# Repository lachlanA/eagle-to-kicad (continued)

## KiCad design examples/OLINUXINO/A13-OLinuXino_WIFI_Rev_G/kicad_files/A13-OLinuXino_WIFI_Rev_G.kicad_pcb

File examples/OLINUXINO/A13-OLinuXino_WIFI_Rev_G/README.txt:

NOTE: ***** USE AT YOUR OWN RISK *****

This contains the eagle file's from OLIMEX/OLINUXINO from github, which have been Renumbered to work with KiCad
as KiCad will not work correctly with out parts reference ending in a number.
Also note the Eagle files have been converted to version 6.xx of eagle.

*** NOTE: you have to enable LIB prifix in the eagle6xx-sch-to-kicad-sch.ulp even thou is shows you don't need it.
          for some reson Ealge has a lib part which has the same name, as the ground part,  but dose not show up
          when the script searchs for conflicking part names, but show's up on the lib !!!  go figure !!!  ****

source of this project example is at Github address:
   https://github.com/OLIMEX/OLINUXINO/tree/master/HARDWARE/A13-OLinuXino

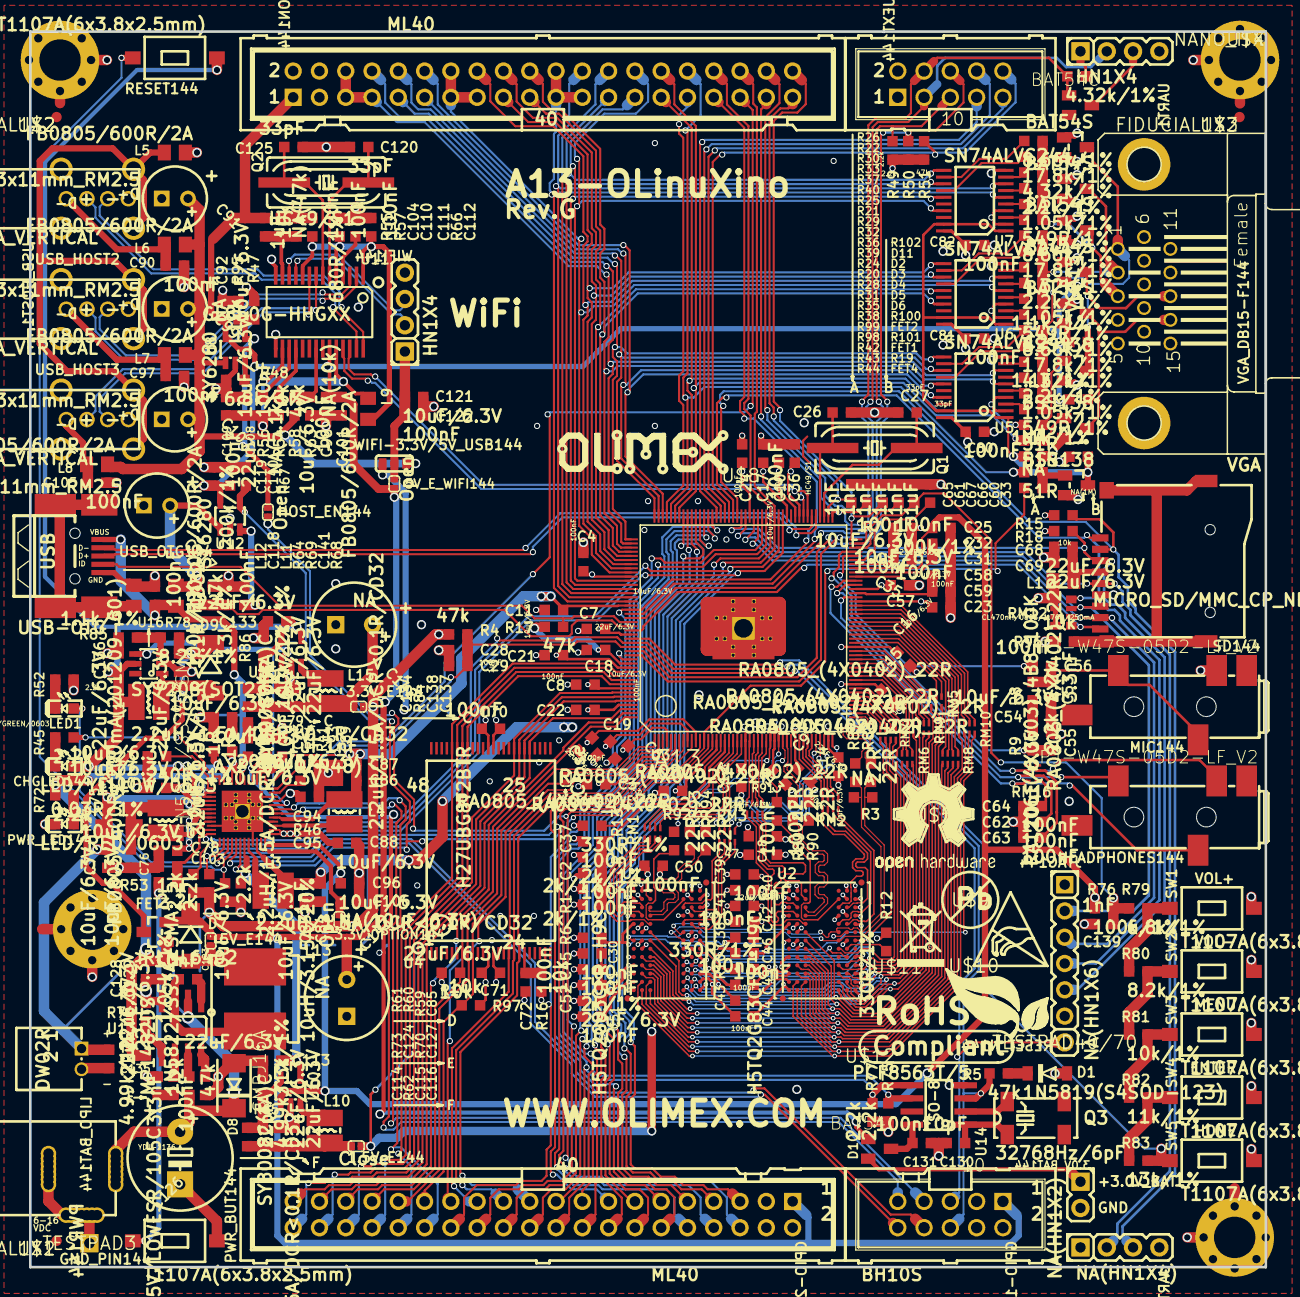
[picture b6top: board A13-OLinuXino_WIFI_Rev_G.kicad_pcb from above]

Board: 4 copper layers, 119.4 x 119.4 mm, 368 parts (0 on the bottom side), 326 nets.

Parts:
1.5V_E144, 3.3V_E144: Close; SJ_1_SMALLER_CLOSE
3.0V_BAT144: NA(HN1X2); HN1X2
3.3V_OPTION144, 5V_E144, 5V_E_WIFI144: Open; SJ_1_SMALLER
C1, C2, C3, C4, C13, C15, C17, C19, C20, C21, C22, C23, C24, C29, C30, C32, C34, C36, C37, C38, C39, C40, C41, C43, C44, C45, C46, C47, C48, C49, C50, C51, C56, C57, C59, C62, C63, C64, C70, C72, C80, C81, C82, C90, C97, C101, C105, C108, C110, C111, C112, C118, C119, C122, C127, C131, C141: 100nF; C0603_DWS
C5, C9, C12, C18, C25, C42, C52, C68, C69, C71, C113, C115, C116, C128, C129, C132, C133, C135, C136, C137, C138: 22uF/6.3V; C0603_DWS
C6, C7, C8, C10, C11, C14, C16, C31, C35, C54, C55, C58, C73, C74, C76, C77, C78, C79, C83, C85, C86, C88, C92, C93, C95, C96, C98, C100, C102, C109, C121: 10uF/6.3V; C0603_DWS
C26, C27, C120, C125: 33pF; C0603_DWS
C28, C33, C75, C89, C94, C104: 1uF; C0603_DWS
C53, C124: 3.3nF; C0603_DWS
C60, C61, C65, C66, C67, C84, C87, C103, C139: 1nF; C0603_DWS
C91, C99, C107, C117: 100uF/16V/LOWESR/105C/6.3x11mm_RM2.5; E2,5-6,3
C106: NA(10uF/6.3V); C0603_DWS
C114: 22pF; C0603_DWS
C123: 10nF; C0603_DWS
C126: 470uF/25V/LOWESR/105C; E5-10,5
C130: 10pF; C0603_DWS
C134: 47pF; C0603_DWS
C140: 22uF; C0603_DWS
C142, C143: NA; E3,5-8
CHGLED144: LED/YELLOW/0603; LED-0603
D1: 1N5819(S4SOD-123); SOD-123
D2, D3, D4, D5, D6: BAT54S; SOT23C(BAT54S)
D7: 1N5822/SS34/SMA; MLL-41
D8: SMBJ16A; DO214AA
D9: 1N5822/SS34/SMA; MELF-MLL41
D10, D11: BAT54C; SOT23C
FET1, FET2, FET4: BSS138; SOT23
FET3: IRLML6402; SOT23
GND_PIN144: TESTPAD3; TEST_PAD40%2f70%2fSQUARE
GPIO-1: BH10S; ML10-MALE
GPIO-2: ML40
HEADPHONES144: PJ-W47S-05D2-LF_V2; PJ-W47S-05D2-LF_5PIN_V2
HOST_EN144: Open; SJ_1_SMALLER
JTAG144: NA(HN1X6); HN1X6
L1: CL470nH/0805/1.76R/250mA; L0805_5MIL_DWS
L2, L3, L4, L10, L14, L15: 2.2uH/1.5A/DCR<0.1R/CD32; CD32
L5, L6, L7, L8, L9, L11: FB0805/600R/2A; L0805_5MIL_DWS
L12: FB0805/600R/200mA(201209-601); L0805_5MIL_DWS
L13: 10uH/3.15A/20%; 8X8MM_3131
LCD_CON144: ML40
LED1: LED/GREEN/0603; LED-0603
LIPO_BAT144: DW02R
MIC144: PJ-W47S-05D2-LF_V2; PJ-W47S-05D2-LF_5PIN_V2
P0, P1, P2, P3, P4, P5, P6, P7, P8, P9, P10, P11, P12: TESTPADTESTPAD_40-ROUND; TESTPAD_40-ROUND
PWR144: YDJ-1136; PWR_JACK_UNI_MILLING
PWR_BUT144: T1107A(6x3.8x2.5mm); SW-TAKT_6X3.5_SMD
PWR_LED144: LED/RED/0603; LED-0603
Q1, Q2: HC49/S1; HC49%2fSMD2_THIN
Q3: 32768Hz/6pF; MC-306
R1, R2, R6, R11: 2k/1%; R0603_5MIL_DWS
R3, R42, R44, R95: NA; R0603_5MIL_DWS
R4, R5, R17, R51, R54, R64, R70: 47k; R0603_5MIL_DWS
R7, R46, R67: 200k/1%; R0603_5MIL_DWS
R8, R9, R45, R49, R50, R52, R53, R59, R60, R61, R72, R73, R75, R77: 2.2k; R0603_5MIL_DWS
R10, R12, R13: 330R/1%; R0603_5MIL_DWS
R14, R16, R18, R47, R55, R56, R96, R97: 10k; R0603_5MIL_DWS
R15: NA(1M); R0603_5MIL_DWS
R19, R85, R100, R101: 1.1k/1%; R0603_5MIL_DWS
R20, R21, R22: 17.8k/1%; R0603_5MIL_DWS
R23: 240R/1%; R0603_5MIL_DWS
R24, R25, R26: 8.66k/1%; R0603_5MIL_DWS
R27: 0.03R/1%; R1206_5MIL_WS
R28, R29, R30, R102: 4.32k/1%; R0603_5MIL_DWS
R31, R32, R33: 2.2k/1%; R0603_5MIL_DWS
R34, R41: 1R; R0603_5MIL_DWS
R35, R36, R37, R74: 1.05k/1%; R0603_5MIL_DWS
R38, R39, R40: 549R/1%; R0603_5MIL_DWS
R43, R98, R99: 51R; R0603_5MIL_DWS
R48, R79: 6.8k/1%; R0603_5MIL_DWS
R57: NA(47k); R0603_5MIL_DWS
R58: NA(5.1k); R0603_5MIL_DWS
R62, R71: 4.99k/1%; R0603_5MIL_DWS
R63: NA(10k); R0603_5MIL_DWS
R65: 3.3k/1%; R0603_5MIL_DWS
R66: 680R/1%; R0603_5MIL_DWS
R68, R83: 13k/1%; R0603_5MIL_DWS
R69, R76, R84: 100k/1%; R0603_5MIL_DWS
R78, R80: 8.2k/1%; R0603_5MIL_DWS
R81: 10k/1%; R0603_5MIL_DWS
R82: 11k/1%; R0603_5MIL_DWS
R86: 22k/1%; R0603_5MIL_DWS
R87, R88, R89, R90, R91, R92, R93, R94: 22R; R0603_5MIL_DWS
RESET144: T1107A(6x3.8x2.5mm); SW-TAKT_6X3.5_SMD
RESET_N144: TESTPAD40/70; TESTPAD
RM1, RM2, RM3, RM4, RM5, RM6, RM7, RM8, RM9, RM10, RM16: RA0805_(4X0402)_22R; R_MATRIX_4_0402_25X625
RM12: RA1206_(4X0603)_4B8_100K; R_MATRIX_4
SD144: MICRO_SD/MMC_CP_NEWTFC-WPAPR-08; TFC-WPAPR-08
SW1, SW2, SW3, SW4, SW5: T1107A(6x3.8x2.5mm); SW-TAKT_6X3.5_SMD
U1, U2: H5TQ2G83CFR-H9C; FBGA78
U3: A13; TQFP176
U4: H27UBG8T2BTR; TSOP48
U5, U6, U7: SN74ALVC244; PW
U8, U12: SY6280; SOT23-5
U9: AXP209(QFN48); QFN48
U10, U15: SY8008C(AA)C; SOT23-5
U11: GL850G-HHGXX; SSOP28
U13: MP1482DS; SOIC8
U14: PCF8563T/5; SO-8
U16: SY7208(SOT23-6); SOT23-6
U$1, U$2, U$3: FIDUCIAL1X2; FIDUCIAL-1X2
U$4: NANO_ITX; NANO-ITX_120X120
U$5: LOGO-OPENHARDWARE_8X8
U$6, U$8: OLIMEX1_V
U$9: PB
U$10: ESD_SYMBOL
U$11: RECYCLE_BIN1%2f8
U$12: ROHS
UART0: NA(HN1X4); HN1X4
UART1: HN1X4
UEXT144: BH10S; ML10-MALE
USB_HOST1, USB_HOST2, USB_HOST3: USB_A_VERTICAL; USB_A_VERTICAL_PTH
USB_OTG144: USB-OTG; USB_MINI_9PIN
VGA_DB15-F144: VGA15; DB15-F_22MM
WIFI144: HN1X4
WIFI-3.3V/5V_USB144: SJ_2_SMALL_12_TIED

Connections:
/#OVCUR1: R58.1, R63.2, U11.21
/+5V: 5V_E144.2, 5V_E_WIFI144.1, C92.1, C98.1, C101.1, C119.1, C140.1, C143.+, D5.2, D6.2, D7.K, FET3.2, GPIO-1.1, GPIO-2.1, LCD_CON144.1, P6.1, R55.2, R100.2, R101.2, U8.5, U11.23, U12.5
/+5V_OTG_PWR: C118.1, L11.1, P12.1, R41.2, U9.31, USB_OTG144.VBUS
/+15V: 5V_E144.1, C128.1, C129.1, D7.A, FET3.1, L13.2, P9.1, R34.2, R71.2, R72.1, U9.32, U9.33
/+24V: C75.2, C77.1, C135.2, LIPO_BAT144.1, P10.1, R27.2, U9.38, U9.39, U9.42
/A0: RM5.1.2, U1.K3, U2.K3
/A1: RM6.3.2, U1.L7, U2.L7
/A2: RM8.3.2, U1.L3, U2.L3
/A3: RM8.4.2, U1.K2, U2.K2
/A4: RM6.4.2, U1.L8, U2.L8
/A5: RM8.2.2, U1.L2, U2.L2
/A6: RM6.2.2, U1.M8, U2.M8
/A7: RM10.2.2, U1.M2, U2.M2
/A8: RM6.1.2, U1.N8, U2.N8
/A9: RM10.4.2, U1.M3, U2.M3
/A10: RM7.3.2, U1.H7, U2.H7
/A11: RM9.4.2, U1.M7, U2.M7
/A12: RM7.1.2, U1.K7, U2.K7
/A13: RM8.1.2, U1.N3, U2.N3
/A14: RM9.3.2, U1.N7, U2.N7
/AVDD: C110.1, C111.1, C112.1, L9.2, U11.1, U11.5, U11.10
/BA0: RM5.2.2, U1.J2, U2.J2
/BA1: RM7.2.2, U1.K8, U2.K8
/BA2: RM5.3.2, U1.J3, U2.J3
/CASN: RM9.1.2, U1.G3, U2.G3
/CKE: RM7.4.2, U1.G9, U2.G9
/CLK: R3.2, R87.1, U1.F7, U2.F7
/CLKN: R3.1, R88.1, U1.G7, U2.G7
/D0: RM1.1.2, U1.B3
/D1: RM3.4.2, U1.C7
/D2: RM1.2.2, U1.C2
/D3: RM3.3.2, U1.C8
/D4: RM1.4.2, U1.E3
/D5: RM3.1.2, U1.E8
/D6: RM1.3.2, U1.D2
/D7: RM3.2.2, U1.E7
/D8: RM2.3.2, U2.C8
/D9: RM4.3.2, U2.D2
/D10: RM2.1.2, U2.E8
/D11: RM4.4.2, U2.E3
/D12: RM2.4.2, U2.C7
/D13: RM4.2.2, U2.C2
/D14: RM2.2.2, U2.E7
/D15: RM4.1.2, U2.B3
/DDR3_A0: RM5.1.1, U3.64
/DDR3_A1: RM6.3.1, U3.52
/DDR3_A2: RM8.3.1, U3.66
/DDR3_A3: RM8.4.1, U3.65
/DDR3_A4: RM6.4.1, U3.51
/DDR3_A5: RM8.2.1, U3.67
/DDR3_A6: RM6.2.1, U3.54
/DDR3_A7: RM10.2.1, U3.71
/DDR3_A8: RM6.1.1, U3.55
/DDR3_A9: RM10.4.1, U3.69
/DDR3_A10: RM7.3.1, U3.48
/DDR3_A11: RM9.4.1, U3.56
/DDR3_A12: RM7.1.1, U3.50
/DDR3_A13: RM8.1.1, U3.68
/DDR3_A14: RM9.3.1, U3.57
/DDR3_BA0: RM5.2.1, U3.63
/DDR3_BA1: RM7.2.1, U3.49
/DDR3_BA2: RM5.3.1, U3.61
/DDR3_CAS: RM9.1.1, U3.59
/DDR3_CK: R87.2, U3.45
/DDR3_CKE: RM7.4.1, U3.47
/DDR3_CK_N: R88.2, U3.46
/DDR3_D0: RM1.1.1, U3.22
/DDR3_D1: RM3.4.1, U3.40
/DDR3_D2: RM1.2.1, U3.21
/DDR3_D3: RM3.3.1, U3.41
/DDR3_D4: RM1.4.1, U3.19
/DDR3_D5: RM3.1.1, U3.44
/DDR3_D6: RM1.3.1, U3.20
/DDR3_D7: RM3.2.1, U3.42
/DDR3_D8: RM2.3.1, U3.37
/DDR3_D9: RM4.3.1, U3.25
/DDR3_D10: RM2.1.1, U3.39
/DDR3_D11: RM4.4.1, U3.24
/DDR3_D12: RM2.4.1, U3.36
/DDR3_D13: RM4.2.1, U3.26
/DDR3_D14: RM2.2.1, U3.38
/DDR3_D15: RM4.1.1, U3.27
/DDR3_DM0: R92.2, U3.29
/DDR3_DM1: R91.2, U3.28
/DDR3_DQS0: R93.2, U3.31
/DDR3_DQS0_N: R94.2, U3.32
/DDR3_DQS1: R89.2, U3.33
/DDR3_DQS1_N: R90.2, U3.34
/DDR3_ODT: RM10.1.2, U1.G1, U2.G1
/DDR3_ODTT: RM10.1.1, U3.72
/DDR3_RAS: RM9.2.1, U3.58
/DDR3_RST: RM10.3.2, U1.N2, U2.N2
/DDR3_RSTT: RM10.3.1, U3.70
/DDR3_WE: RM5.4.1, U3.60
/DM1: U11.27, USB_HOST1.2
/DM2: U11.2, USB_HOST2.2
/DM3: U11.8, USB_HOST3.2
/DM4: U11.11, WIFI144.2
/DP1: U11.28, USB_HOST1.3
/DP2: U11.3, USB_HOST2.3
/DP3: U11.9, USB_HOST3.3
/DP4: U11.12, WIFI144.3
/DQM0: R92.1, U1.B7
/DQM1: R91.1, U2.B7
/DQS0: R93.1, U1.C3
/DQS0_N: R94.1, U1.D3
/DQS1: R89.1, U2.C3
/DQS1_N: R90.1, U2.D3
/DVDD: C108.1, C109.1, L9.1, R54.1, R56.1, U11.16, U11.24
/DZQ: R13.2, U3.17
/EXTEN: U9.20, U15.1, U16.4
/GND: 3.0V_BAT144.2, C2.1, C3.1, C4.1, C5.1, C6.1, C7.1, C8.1, C9.1, C10.1, C11.1, C12.1, C13.1, C14.1, C15.1, C16.1, C17.1, C18.1, C19.1, C20.1, C21.1, C22.1, C23.1, C24.1, C25.1, C26.1, C27.1, C28.1, C29.1, C31.1, C32.1, C33.1, C34.1, C35.1, C36.1, C37.1, C38.1, C39.1, C40.1, C41.1, C42.1, C43.1, C44.1, C45.1, C46.1, C47.1, C48.1, C49.1, C50.1, C51.1, C52.1, C53.1, C54.1, C55.1, C57.1, C58.1, C59.1, C60.1, C61.1, C62.1, C63.1, C64.1, C65.1, C66.1, C67.1, C68.1, C69.1, C70.1, C71.1, C72.1, C73.1, C74.1, C76.2, C77.2, C78.2, C79.1, C80.2, C81.2, C82.2, C83.2, C84.2, C85.2, C86.2, C87.2, C88.2, C89.1, C90.2, C91.-, C92.2, C93.2, C94.1, C95.1, C96.2, C97.2, C98.2, C99.-, C100.2, C101.2, C102.2, C103.1, C104.1, C105.2, C106.2, C107.-, C108.2, C109.2, C110.2, C111.2, C112.2, C113.2, C115.2, C116.2, C117.-, C118.2, C119.2, C120.1, C121.2, C122.2, C125.1, C126.-, C127.2, C128.2, C129.2, C130.2, C131.1, C132.2, C133.2, C135.1, C136.1, C137.2, C138.2, C139.2, C140.2, C141.2, C142.-, C143.-, D2.1, D3.1, D4.1, D5.1, D6.1, D8.A, GND_PIN144.P$1, GPIO-1.2, GPIO-1.4, GPIO-2.2, GPIO-2.4, JTAG144.6, L5.1, L12.1, LCD_CON144.2, LCD_CON144.4, LIPO_BAT144.2, MIC144.5, P0.1, PWR144.-, PWR144.--, PWR_BUT144.P$1, PWR_LED144.C, R2.1, R7.2, R10.1, R11.1, R12.1, R13.1, R15.2, R23.1, R42.1, R46.1, R48.1, R52.1, R57.2, R59.1, R63.1, R65.2, R66.1, R67.1, R68.1, R69.1, R73.2, R74.2, R85.2, R86.2, R95.1, R96.2, SD144.6, SW1.P$1, SW2.P$1, SW3.P$1, SW4.P$1, SW5.P$1, U1.A1, U1.A8, U1.B1, U1.B2, U1.B8, U1.C9, U1.D1, U1.D8, U1.D9, U1.F2, U1.F8, U1.H2, U1.J1, U1.J9, U1.L1, U1.L9, U1.N1, U1.N9, U2.A1, U2.A8, U2.B1, U2.B2, U2.B8, U2.C9, U2.D1, U2.D8, U2.D9, U2.F2, U2.F8, U2.H2, U2.J1, U2.J9, U2.L1, U2.L9, U2.N1, U2.N9, U3.79, U3.GND_, U4.13, U4.36, U5.2, U5.4, U5.10, U6.2, U6.4, U6.10, U7.2, U7.4, U7.10, U8.2, U9.9, U9.16, U9.22, U9.46, U9.VSS, U10.2, U11.14, U11.15, U12.2, U13.4, U14.4, U15.2, U16.2, U$4.GND, U$4.P$2, U$4.P$3, U$4.P$4, UART0.4, UART1.4, UEXT144.2, USB_HOST1.4, USB_HOST2.4, USB_HOST3.4, USB_OTG144.GND, VGA_DB15-F144.5, VGA_DB15-F144.6, VGA_DB15-F144.7, VGA_DB15-F144.8, VGA_DB15-F144.10, WIFI144.4
/IPSOUT: C73.2, C78.1, C85.1, C88.1, C95.2, C102.1, C113.1, C133.1, C136.2, CHGLED144.A, L14.1, P5.1, RESET144.P$2, U9.7, U9.13, U9.14, U9.21, U9.34, U9.35, U9.40, U9.44, U10.4, U15.4, U16.5
/LCD_CLK: LCD_CON144.31, U3.129
/LCD_D2: LCD_CON144.21, LCD_CON144.22, LCD_CON144.23, U3.148, U7.6
/LCD_D3: LCD_CON144.24, U3.147, U7.8
/LCD_D4: LCD_CON144.25, U3.146, U7.11
/LCD_D5: LCD_CON144.26, U3.145, U7.13
/LCD_D6: LCD_CON144.27, U3.144, U7.15
/LCD_D7: LCD_CON144.28, U3.143, U7.17
/LCD_D10: LCD_CON144.13, LCD_CON144.14, LCD_CON144.15, U3.141, U6.6
/LCD_D11: LCD_CON144.16, U3.140, U6.8
/LCD_D12: LCD_CON144.17, U3.139, U6.11
/LCD_D13: LCD_CON144.18, U3.138, U6.13
/LCD_D14: LCD_CON144.19, U3.137, U6.15
/LCD_D15: LCD_CON144.20, U3.136, U6.17
/LCD_D18: LCD_CON144.5, LCD_CON144.6, LCD_CON144.7, U3.135, U5.6
/LCD_D19: LCD_CON144.8, U3.134, U5.8
/LCD_D20: LCD_CON144.9, U3.133, U5.11
/LCD_D21: LCD_CON144.10, U3.132, U5.13
/LCD_D22: LCD_CON144.11, U3.131, U5.15
/LCD_D23: LCD_CON144.12, U3.130, U5.17
/LCD_DE: LCD_CON144.32, R43.1, U3.128
/LCD_HSYNC: LCD_CON144.29, R99.1, U3.127
/LCD_VSYNC: LCD_CON144.30, R98.1, U3.126
/LRADC: C60.2, C139.1, R76.2, R79.1, U3.86
/N$1: C58.2, C59.2, U3.75
/N$2: C30.2, C38.2, C45.2, C46.2, R6.1, R11.2, U1.E1, U1.J8, U2.E1, U2.J8
/N$3: R10.2, U1.H8
/N$4: R45.2, U9.36
/N$5: R12.2, U2.H8
/N$6: HOST_EN144.2, R47.2, R95.2, U8.4
/N$7: R96.1, SD144.10, SD144.11, SD144.12, SD144.13
/N$8: L10.1, U10.3
/N$9: C31.2, C32.2, U3.80
/N$11: 5V_E_WIFI144.2, C121.1, C122.1, WIFI144.1, WIFI-3.3V/5V_USB144.2
/N$13: C33.2, U3.83
/N$14: C34.2, C35.2, R7.1, U3.82
/N$16: C53.2, C56.1, MIC144.2, MIC144.3, R8.2
/N$18: 1.5V_E144.1, C114.1, C115.1, C116.1, L10.2, R62.1
/N$19: C114.2, R62.2, R65.1, U10.5
/N$20: R37.1, U7.5
/N$21: R43.2, R44.1
/N$22: C54.2, R8.1, R9.2
/N$23: C132.1, D9.1, FET3.3, R78.2
/N$24: C131.2, D10.3, U14.8
/N$25: C56.2, U3.84
/N$26: HEADPHONES144.2, RM16.2.2, U3.74
/N$27: HEADPHONES144.5, RM16.3.2, U3.77
/N$28: HEADPHONES144.3, RM16.1.2, U3.78
/N$29: 3.0V_BAT144.1, D10.2
/N$30: D11.3, UART1.3
/N$31: C126.+, D8.C, P8.1, PWR144.+, R70.1, U13.2
/N$34: C62.2, RM16.2.1
/N$35: C63.2, RM16.3.1
/N$36: C127.1, U13.8
/N$37: R70.2, U13.7
/N$38: PWR_BUT144.P$2, R53.1
/N$42: LED1.C, R52.2
/N$43: CHGLED144.C, R45.1
/N$44: C64.2, RM16.1.1
/N$46: C123.1, U13.1
/N$50: C123.2, L13.1, U13.3
/N$60: C124.1, U13.6
/N$61: C124.2, R73.1
/N$62: R71.1, R74.1, U13.5
/N$64: L15.1, U15.3
/N$65: 3.3V_E144.1, C134.1, C137.1, C138.1, C142.+, L15.2, R84.1
/N$66: C134.2, R84.2, R86.1, U15.5
/N$88: R79.2, R80.1, SW1.P$2
/N$89: R80.2, R81.1, SW2.P$2
/N$90: R81.2, R82.1, SW3.P$2
/N$91: R82.2, R83.1, SW4.P$2
/N$99: R68.2, U12.3
/N$100: C117.+, L11.2, R64.2, U12.1
/N$101: R48.2, U8.3
/N$102: R66.2, U11.4
/N$103: R40.1, U7.3
/N$104: R30.1, U7.9
/N$105: R54.2, U11.18
/N$106: R56.2, U11.17
/N$107: R33.1, U7.7
/N$108: R22.1, U7.14
/N$109: R26.1, U7.12
/N$110: L5.2, USB_HOST1.P$3, USB_HOST1.P$4, USB_HOST2.P$3, USB_HOST2.P$4, USB_HOST3.P$3, USB_HOST3.P$4
/N$111: C90.1, L6.2, USB_HOST1.1
/N$112: C97.1, L7.2, USB_HOST2.1
/N$113: C105.1, L8.2, USB_HOST3.1
/N$114: C91.+, C99.+, C107.+, L6.1, L7.1, L8.1, R58.2, U8.1, WIFI-3.3V/5V_USB144.1
/N$117: R29.1, U6.9
/N$118: R32.1, U6.7
/N$119: C104.2, R55.1, R57.1, U11.13
/N$120: R46.2, U9.23
/N$121: C130.1, Q3.1, U14.1
/N$122: Q3.4, U14.2
/N$123: D9.2, L14.2, U16.1
/N$124: C72.2, R16.2, U4.19
/N$125: R23.2, U9.37
/N$126: R78.1, R85.1, U16.3
/N$127: L2.1, U9.45
/N$128: C75.1, C76.1, L2.2, R27.1, U9.43
/N$129: PWR_LED144.A, R72.2
/N$130: L3.1, U9.8
/N$131: L4.1, U9.15
/N$132: C94.2, U9.24
/N$133: 3.3V_OPTION144.1, C106.1, U9.11
/N$134: C74.2, R34.1
/N$135: C79.2, R41.1
/N$138: R36.1, U6.5
/N$139: C103.2, R53.2, U9.47
/N$140: R59.2, RESET144.P$1, U9.4
/N$172: R39.1, U6.3
/N$173: R21.1, U6.14
/N$174: R25.1, U6.12
/N$177: R28.1, U5.9
/N$178: R31.1, U5.7
/N$179: R35.1, U5.5
/N$180: R38.1, U5.3
/N$181: R20.1, U5.14
/N$182: R24.1, U5.12
/N$266: L12.2, USB_OTG144.GND1, USB_OTG144.GND2, USB_OTG144.GND3, USB_OTG144.GND4
/NMI_N: GPIO-1.6, R5.1, U3.158, U9.48, U14.3
/PIN0: GPIO-1.7, LCD_CON144.35, U9.19
/PIN1: GPIO-1.9, U9.18
/PIN2: GPIO-1.10, U9.5
/PIN3: GPIO-1.8, U9.3
/PIN4/TWI0-SCK: GPIO-2.5, R60.1, U3.101, U9.2
/PIN5/TWI0-SDA: GPIO-2.7, R61.1, U3.102, U9.1
/PIN6/PWM0: GPIO-2.9, LCD_CON144.36, U3.103
/PIN7: GPIO-2.11, LCD_CON144.33, U3.150
/PIN8: GPIO-2.13, LCD_CON144.34, U3.104
/PIN9: GPIO-2.15, U3.10
/PIN10/TWI1-SCK: GPIO-2.17, R75.1, U3.105, U14.6
/PIN11/TWI1-SDA: GPIO-2.19, R77.1, U3.106, U14.5
/PIN12/NWE: GPIO-2.21, U3.8, U4.18
/PIN13/NALE: GPIO-2.23, U3.7, U4.17
/PIN14/NCLE: GPIO-2.25, U3.6, U4.16
/PIN15/NCE1: GPIO-2.27, U3.3
/PIN16/NCE0: GPIO-2.29, R97.2, U4.9
/PIN17/NRE: GPIO-2.31, U3.1, U4.8
/PIN18/NRB0: GPIO-2.33, R14.2, U3.176, U4.7
/PIN19/NRB1: GPIO-2.35, U3.175
/PIN20/NDQ0: GPIO-2.37, U3.174, U4.29
/PIN21/NDQ1: GPIO-2.39, U3.172, U4.30
/PIN22/NDQ2: GPIO-2.40, U3.171, U4.31
/PIN23/NDQ3: GPIO-2.38, U3.170, U4.32
/PIN24/NDQ4: GPIO-2.36, U3.168, U4.41
/PIN25/NDQ5: GPIO-2.34, U3.167, U4.42
/PIN26/NDQ6: GPIO-2.32, U3.166, U4.43
/PIN27/NDQ7: GPIO-2.30, U3.165, U4.44
/PIN28/NDQS: GPIO-2.28, U3.162
/PIN29: GPIO-2.26, U3.118
/PIN30: GPIO-2.24, U3.119
/PIN31: GPIO-2.22, U3.120
/PIN32: GPIO-2.20, U3.121
/PIN33: GPIO-2.18, U3.122
/PIN34: GPIO-2.16, U3.123
/PIN35: GPIO-2.14, U3.124
/PIN36: GPIO-2.12, U3.125
/PIN37/LED1: GPIO-2.10, LED1.A, U3.12
/PIN38/VGA_DIS: GPIO-2.8, R44.2, U3.13
/PIN39/USBH_EN: GPIO-2.6, HOST_EN144.1, U3.14
/RASN: RM9.2.2, U1.F3, U2.F3
/RESET_N: C28.2, C29.2, GPIO-1.5, R4.1, RESET_N144.P$1, U3.159, U9.25
/SD0CARD-DETECT: RM12.4.2, SD144.9, U3.155
/SDC0_CMD: JTAG144.5, R18.1, SD144.3, U3.111
/SDC0_DATA0: JTAG144.2, RM12.2.2, SD144.7, U3.108
/SDC0_DATA1: JTAG144.3, RM12.3.2, SD144.8, U3.107
/SDC0_DATA2: JTAG144.4, RM12.1.2, SD144.1, U3.113
/SDC0_DATA3: R15.1, SD144.2, U3.112, UART0.3
/SDC0_SCK: SD144.5, U3.110, UART0.2
/SD_VCC: C68.2, C69.2, L1.2, SD144.4
/SPI2_CLK: U3.115, UEXT144.9
/SPI2_CS0: R51.1, U3.114, UEXT144.10
/SPI2_MISO: U3.117, UEXT144.7
/SPI2_MOSI: U3.116, UEXT144.8
/SVREF: C1.2, C2.2, C37.2, R1.1, R2.2, U3.18
/TPX1: C61.2, LCD_CON144.37, U3.89
/TPX2: C66.2, LCD_CON144.38, U3.87
/TPY1: C65.2, LCD_CON144.39, U3.90
/TPY2: C67.2, LCD_CON144.40, U3.88
/TWI2_SCK: R49.1, U3.161, UEXT144.5
/TWI2_SDA: R50.1, U3.160, UEXT144.6
/UART1_RX: D11.1, R102.1, U3.151, UEXT144.4
/UART1_TX: U3.152, UART1.2, UEXT144.3
/UBOOT: R83.2, SW5.P$2, U3.157
/UDM0: U3.93, USB_OTG144.D-
/UDM1: U3.95, U11.25
/UDP0: U3.94, USB_OTG144.D+
/UDP1: U3.96, U11.26
/USB0-DRV: R67.2, U3.15, U9.6, U12.4
/USB0-IDDET: R17.2, U3.153, USB_OTG144.ID
/USB0-VBUSDET: C141.1, R64.1, R69.2, U3.154
/V+: 1.5V_E144.2, C1.1, C12.2, C13.2, C14.2, C15.2, C16.2, C30.1, C39.2, C40.2, C41.2, C42.2, C43.2, C44.2, C47.2, C48.2, C49.2, C50.2, C51.2, C52.2, P1.1, R1.2, R6.2, U1.A2, U1.A9, U1.B9, U1.C1, U1.D7, U1.E2, U1.E9, U1.G2, U1.G8, U1.K1, U1.K9, U1.M1, U1.M9, U2.A2, U2.A9, U2.B9, U2.C1, U2.D7, U2.E2, U2.E9, U2.G2, U2.G8, U2.K1, U2.K9, U2.M1, U2.M9, U3.23, U3.30, U3.43, U3.53, U3.62
/VCC: 3.3V_E144.2, 3.3V_OPTION144.2, C3.2, C4.2, C17.2, C18.2, C36.2, C57.2, C70.2, C71.2, C80.1, C81.1, C82.1, D2.2, D3.2, D4.2, GPIO-1.3, GPIO-2.3, JTAG144.1, L1.1, LCD_CON144.3, P7.1, R4.2, R14.1, R16.1, R17.1, R18.2, R19.2, R47.1, R49.2, R50.2, R51.2, R60.2, R61.2, R75.2, R77.2, R97.1, R102.2, RM12.1.1, RM12.2.1, RM12.3.1, RM12.4.1, U3.5, U3.76, U3.97, U3.100, U3.142, U3.163, U4.12, U4.37, U5.20, U6.20, U7.20, UART0.1, UART1.1, UEXT144.1
/VCC/2: C5.2, C6.2, C7.2, C8.2, C19.2, C20.2, C21.2, C22.2, C83.1, C84.1, L3.2, P3.1, U3.4, U3.9, U3.11, U3.16, U3.156, U3.164, U3.169, U3.173, U9.10
/VCCINT: C9.2, C10.2, C11.2, C23.2, C24.2, C86.1, C87.1, L4.2, P11.1, U3.35, U3.73, U3.98, U3.109, U3.149, U9.17
/VDD_RTC: C93.1, D10.1, P2.1, U9.28
/VGA_B: D4.3, R22.2, R26.2, R30.2, R33.2, R37.2, R40.2, VGA_DB15-F144.3
/VGA_CTRL: R19.1, R42.2, U5.1, U5.19, U6.1, U6.19, U7.1, U7.19
/VGA_G: D3.3, R21.2, R25.2, R29.2, R32.2, R36.2, R39.2, VGA_DB15-F144.2
/VGA_HSYNC: D5.3, R100.1, VGA_DB15-F144.13
/VGA_R: D2.3, R20.2, R24.2, R28.2, R31.2, R35.2, R38.2, VGA_DB15-F144.1
/VGA_VSYNC: D6.3, R101.1, VGA_DB15-F144.14
/VINT: C89.2, U9.26, U9.27
/VMIC: C55.2, R9.1, U3.85
/VPP: C25.2, C96.1, P4.1, R76.1, U3.81, U9.12, U10.1
/WEN: RM5.4.2, U1.H3, U2.H3
/WIFI-3V3: C100.1, U9.41, WIFI-3.3V/5V_USB144.3
/X1: C120.2, Q2.2, U11.6
/X2: C125.2, Q2.1, U11.7
/XTALI: C26.2, Q1.2, U3.92
/XTALO: C27.2, Q1.1, U3.91
GND: FET1.2, FET2.2, FET4.2
unnamed: U3.P$2, U3.P$3, U3.P$4, U3.P$5, U3.P$6, U3.P$7, U3.P$8, U3.P$9, U3.P$10, U3.P$11, U3.P$12, U3.P$13, U3.P$14, U3.P$15, U3.P$16, U3.P$17, U3.P$18
unnamed: U9.N1, U9.N2, U9.N3, U9.N4, U9.N5, U9.N6, U9.N7, U9.N8, U9.N9, U9.N10, U9.N11, U9.N12, U9.N13, U9.N14, U9.N15, U9.N16, U9.N17
